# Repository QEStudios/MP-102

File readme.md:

# MP-102 Macropad

The MP-102 Macropad features 10 MX-compatible keys and 2 rotary encoders with optional buttons. It uses a Raspberry Pi Pico (RP2040) or compatible microcontroller as the brains. It can be constructed by anyone as long as you have a 3D printer.

## Ordering parts

The MP-102 was designed to be built on a budget of around $35 Australian Dollars. Thus, parts were aquired from less reliable places than where you might normally buy them. I've linked the relevant places here as well as in the `Layout and BOM.xlsx` file, but all of the parts are generic and can be bought from wherever you find easiest (or cheapest).

I ordered the Hot Melt Inserts from the link provided quite a while before I started this project, so I didn't personally factor this cost into the price of my own build of the MP-102.

[All prices in Australian Dollars]
| Item                       | Price | Link                                                  |
|----------------------------|-------|-------------------------------------------------------|
| 5pcs Rotary Encoder        | $5.27 | https://www.aliexpress.com/item/1005003070250718.html |
| 10pcs Keycaps              | $4.17 | https://www.aliexpress.com/item/1005005825113345.html |
| 10pcs Key Switches         | $4.61 | https://www.aliexpress.com/item/1005006376024657.html |
| Raspberry Pi Pico          | $4.32 | https://www.aliexpress.com/item/1005006293406528.html |
| 10pcs Hotswap Sockets      | $2.65 | https://www.aliexpress.com/item/1005006737039916.html |
| M2 OD3.5 Holt Melt Inserts | $5.93 | https://www.aliexpress.com/item/1005006465779940.html |
| USB C Cable                | $2.39 | https://www.aliexpress.com/item/1005006065386047.html |
| PCB                        | $5.20 | https://jlcpcb.com/                                   |

## Build Instructions

### 3D Prints

All 3D model files can be found in the `3D Models` folder in this repository.

You might want to first print out `USB C Test Piece.stl` and make sure that your USB cable fits through the hole, as this is the size of the opening to the USB C port on the Pico.

There are two different files for the knobs, one with 0.1mm tolerences and one with 0.2mm tolerences. I recommend printing both and choosing the one which fits better for you. You can also use the horizontal expansion setting in your slicer to fine-tune this to your liking.

All files (excluding `USC C Test Piece.stl`) need to be printed only once, apart from the knob file (either `Knob 0.1mm Clearance.stl` or `Knob 0.2mm Clearance.stl`), which you need to print 2 of.

The top part of the case should slide onto the bottom part of the case. You'll need to insert the hot melt inserts into the two holes on the underside of the top part of the case. 

### PCB

The PCB was designed in KiCad, and the project files for the PCB can be found in the `PCB` folder in this repository.

The gerber files have been included in the `PCB/gerbers` folder, but your mileage may vary when using them. I recommend re-generating the gerbers yourself, just to be safe.

I ordered the PCBs from JLCPCB due to their very low price and shipping costs, but you can use whichever fab house you prefer.

Make sure to order the PCB with a thickness of 1.6mm as the case was designed for a PCB of that size.

### Flashing the Pico

1. Install QMK by following [this guide](https://docs.qmk.fm/newbs_getting_started).
2. Copy the `QMK Definition` folder into your QMK `keyboards` directory, and rename the `QMK Definition` folder to `mp102`.
3. Run `qmk flash -kb mp102 -km default` in the QMK MSYS terminal. When it says it's waiting for the device, plug the Pico into your computer while holding the BOOT button down. QMK should flash the Pico with the correct firmware.

### Assembly

1. Solder all the components onto the PCB. Make sure that the Pico is soldered onto the **underside** of the PCB.
2. Click the keyswitches into the plate. The top 2 rows should be oriented facing upwards (with the pins on the bottom), and the lower row of 2 switches should be oriented facing downwards (with the pins on the top). If you're using keycaps that let you customise their legends, now is a good time to do that.

# TODO: finish documentation

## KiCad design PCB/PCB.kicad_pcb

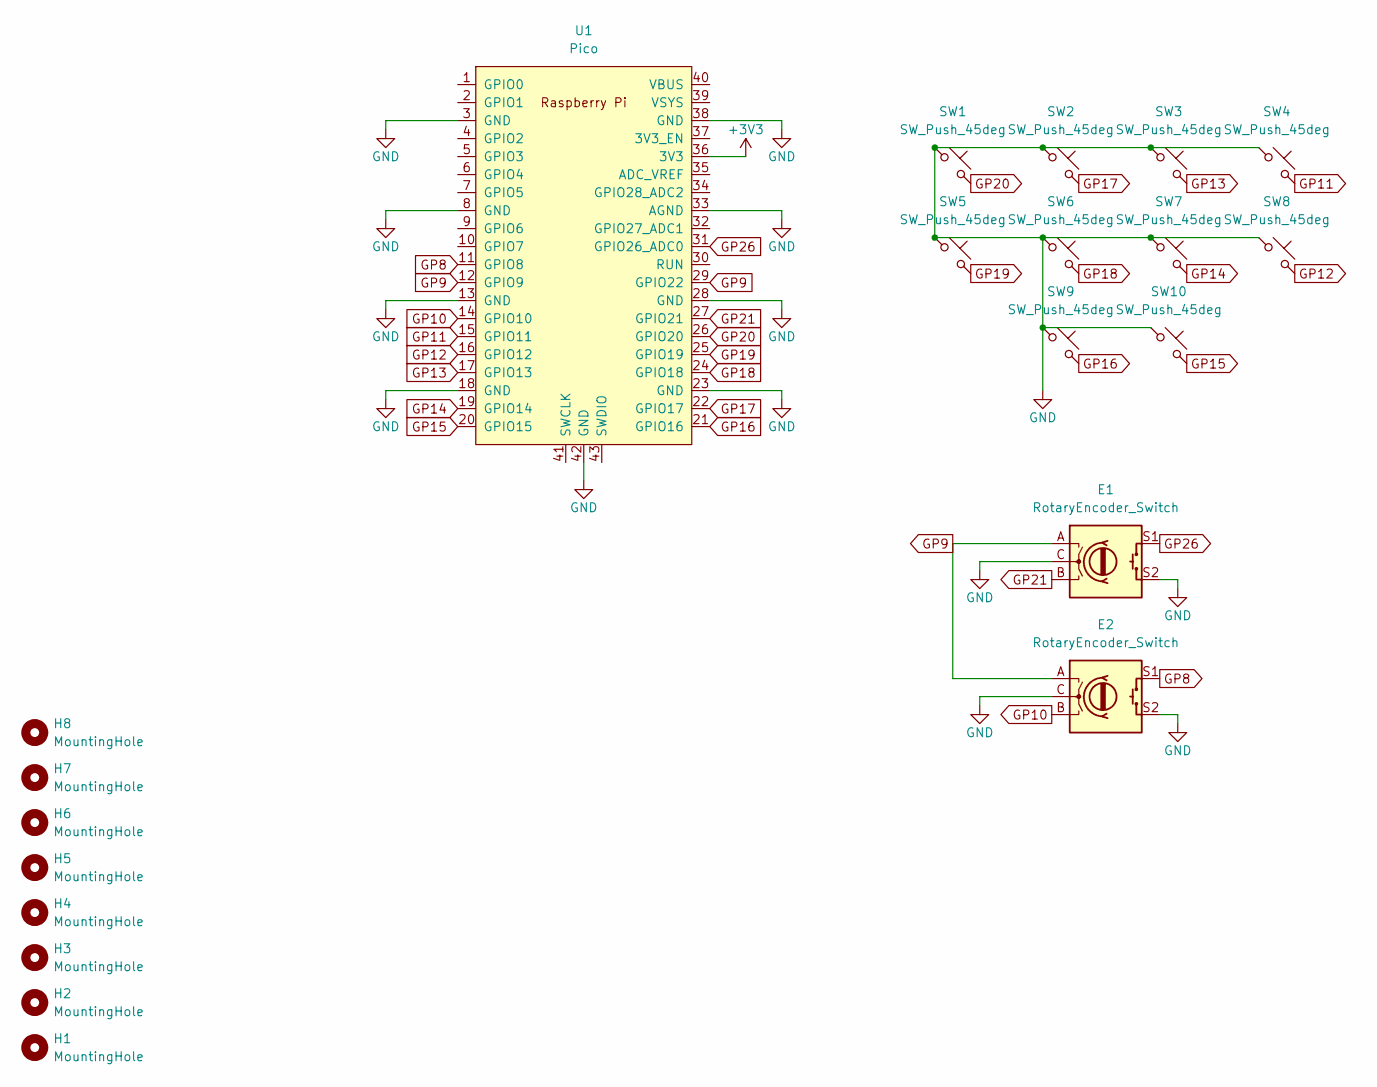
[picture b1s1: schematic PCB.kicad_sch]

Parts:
E1, E2: RotaryEncoder_Switch; RotaryEncoder_Alps_EC12E-Switch_Vertical_H20mm
H1, H2, H3, H4, H5, H6, H7, H8: MountingHole; MountingHole_2.2mm_M2
SW1, SW2, SW3, SW4, SW5, SW6, SW7, SW8, SW9, SW10: SW_Push_45deg; SW_Hotswap_Kailh_MX_1.00u
U1: Pico; RPi_Pico_SMD_TH

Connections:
+3V3: U1.36 (3V3)
GND: E1.C, E1.S2, E2.C, E2.S2, SW1.1, SW2.1, SW3.1, SW4.1, SW5.1, SW6.1, SW7.1, SW8.1, SW9.1, SW10.1, U1.3 (GND), U1.8 (GND), U1.13 (GND), U1.18 (GND), U1.23 (GND), U1.28 (GND), U1.33 (AGND), U1.38 (GND), U1.42 (GND)
GP8: E2.S1, U1.11 (GPIO8)
GP9: E1.A, E2.A, U1.12 (GPIO9), U1.29 (GPIO22)
GP10: E2.B, U1.14 (GPIO10)
GP11: SW4.2, U1.15 (GPIO11)
GP12: SW8.2, U1.16 (GPIO12)
GP13: SW3.2, U1.17 (GPIO13)
GP14: SW7.2, U1.19 (GPIO14)
GP15: SW10.2, U1.20 (GPIO15)
GP16: SW9.2, U1.21 (GPIO16)
GP17: SW2.2, U1.22 (GPIO17)
GP18: SW6.2, U1.24 (GPIO18)
GP19: SW5.2, U1.25 (GPIO19)
GP20: SW1.2, U1.26 (GPIO20)
GP21: E1.B, U1.27 (GPIO21)
GP26: E1.S1, U1.31 (GPIO26_ADC0)

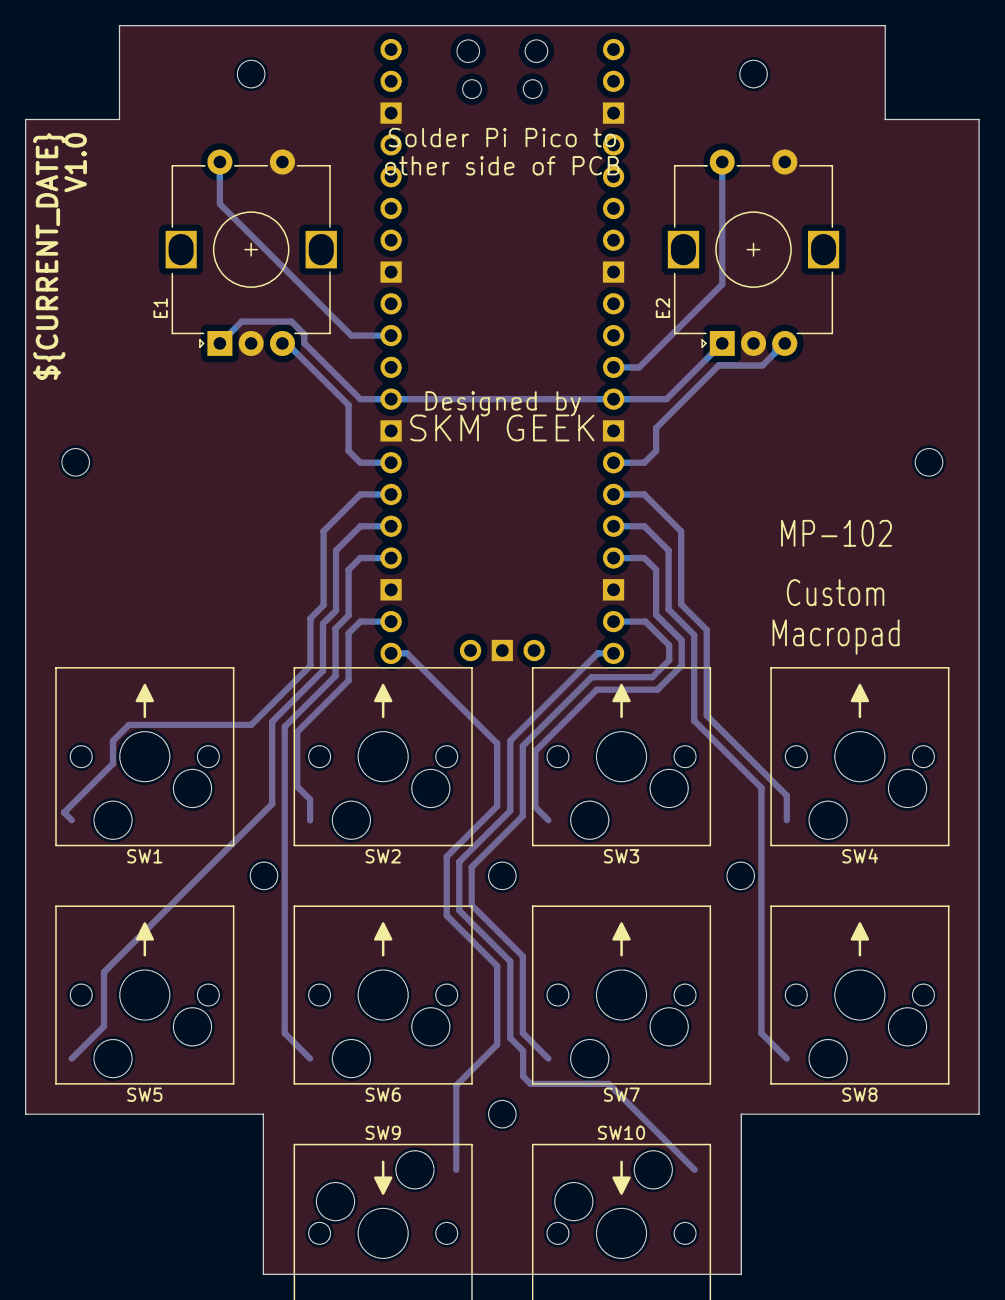
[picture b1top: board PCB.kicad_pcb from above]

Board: 2 copper layers, 76.2 x 99.8 mm, 21 parts (1 on the bottom side), 16 nets.

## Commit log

2024-09-05 Update information
2024-09-05 Fix spacing and unfinished sentence.
2024-09-05 PCB thickness note
